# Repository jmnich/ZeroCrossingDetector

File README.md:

# Zero Crossing Detector (ZCD) 
*Designed for use with Fourier Transform Spectrometers.* 
This device converts symmetric sinusoidal signal from the reference beam detector into a TTL-compatible trigger for acquisition. 

Main features: 
- two TTL outputs 
- one intermediate monitor output
- one input 
- requires an external +-5 V symmetric supply
- accepts signals up to 20 V AC peak-peak +- 10 V DC
- input frequency up to 5 MHz
- hysteresis selectable with a rotary switch from about 20mV up to 2V

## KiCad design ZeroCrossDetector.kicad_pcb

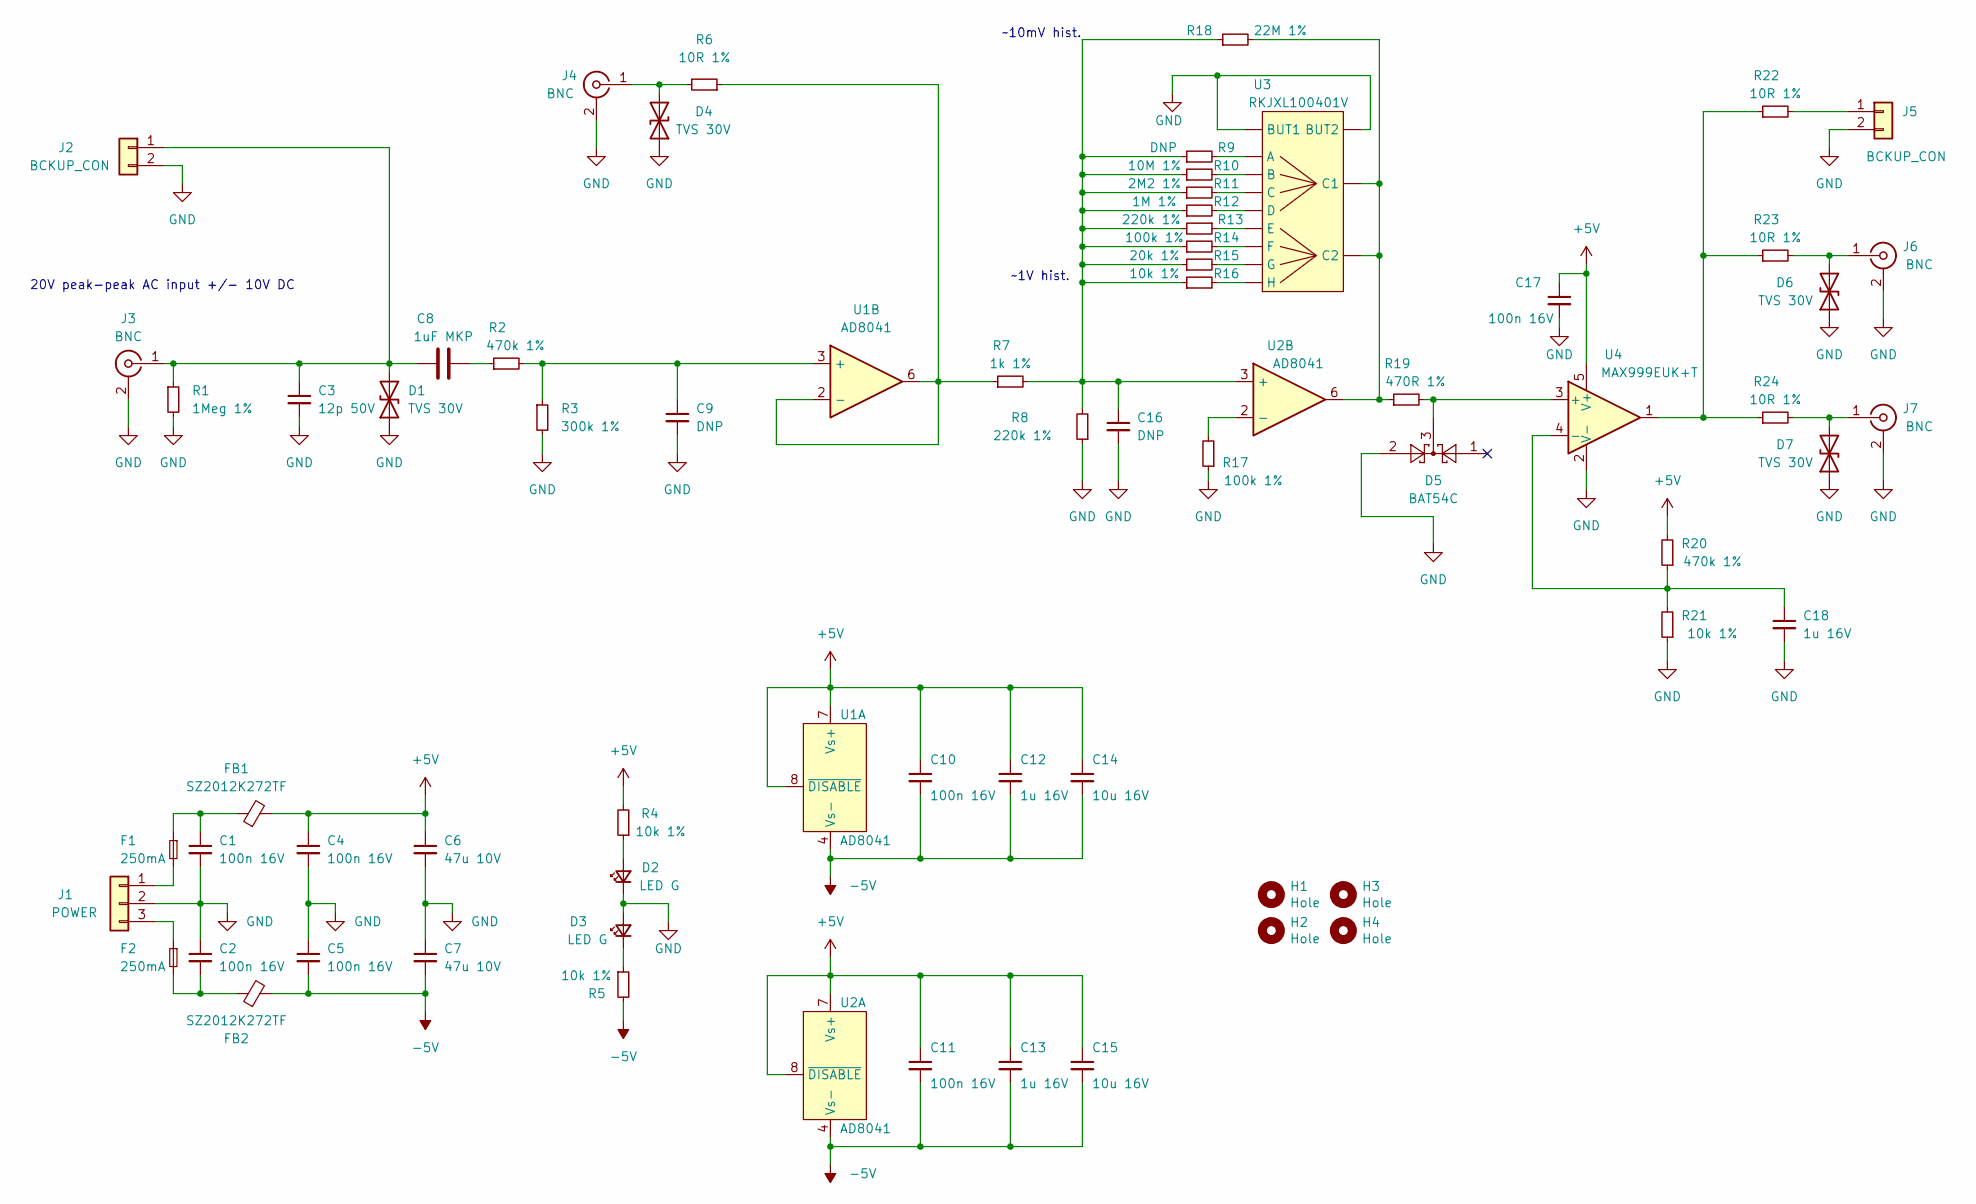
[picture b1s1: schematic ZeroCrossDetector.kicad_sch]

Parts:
C1, C2, C4, C5, C10, C11, C17: 100n 16V; C_0603_1608Metric; JLC C14663
C3: 12p 50V; C_0603_1608Metric; JLC C38523
C6, C7: 47u 10V; C_1206_3216Metric; JLC C96123
C8: 1uF MKP; C_Rect_L7.5mm_W6.5mm_P5.00mm; JLC C514201
C9, C16: DNP; C_0603_1608Metric
C12, C13, C18: 1u 16V; C_0603_1608Metric; JLC C15849
C14, C15: 10u 16V; C_0805_2012Metric; JLC C96446
D1, D4, D6, D7: TVS 30V; D_SMB; MPN SMBJ30CA/TR13; JLC C78418
D2, D3: LED G; LED_0603_1608Metric_Pad1.05x0.95mm_HandSolder; JLC C72043
D5: BAT54C; SOT-23; JLC C37704
F1, F2: 250mA; Fuse_0805_2012Metric_Pad1.15x1.40mm_HandSolder; JLC C269102
FB1, FB2: SZ2012K272TF; L_0805_2012Metric; MPN SZ2012K272TF; JLC C185876
H1, H2, H3, H4: Hole; MountingHole_3.2mm_M3_Pad_Via
J1: POWER; TerminalBlock_Phoenix_MKDS-1,5-3-5.08_1x03_P5.08mm_Horizont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; MPN DG500-5.08-03P-14-00A(H); JLC C581322
J2, J5: BCKUP_CON; PinHeader_1x02_P2.54mm_Vertical
J3, J4, J6, J7: BNC; BNC_Amphenol_B6252HB-NPP3G-50_Horizontal; JLC C2837587
R1: 1Meg 1%; R_0805_2012Metric_Pad1.20x1.40mm_HandSolder; JLC C17514
R2, R20: 470k 1%; R_0805_2012Metric_Pad1.20x1.40mm_HandSolder; JLC C17709
R3: 300k 1%; R_0805_2012Metric_Pad1.20x1.40mm_HandSolder; JLC C17616
R4, R5: 10k 1%; R_0603_1608Metric_Pad0.98x0.95mm_HandSolder; JLC C25804
R6, R22, R23, R24: 10R 1%; R_0805_2012Metric_Pad1.20x1.40mm_HandSolder; JLC C17415
R7: 1k 1%; R_0805_2012Metric_Pad1.20x1.40mm_HandSolder; JLC C17513
R8, R13: 220k 1%; R_0805_2012Metric_Pad1.20x1.40mm_HandSolder; JLC C17556
R9: DNP; R_0805_2012Metric_Pad1.20x1.40mm_HandSolder
R10: 10M 1%; R_0805_2012Metric_Pad1.20x1.40mm_HandSolder; JLC C26108
R11: 2M2 1%; R_0805_2012Metric_Pad1.20x1.40mm_HandSolder; JLC C26113
R12: 1M 1%; R_0805_2012Metric_Pad1.20x1.40mm_HandSolder; JLC C17514
R14, R17: 100k 1%; R_0805_2012Metric_Pad1.20x1.40mm_HandSolder; JLC C149504
R15: 20k 1%; R_0805_2012Metric_Pad1.20x1.40mm_HandSolder; JLC C4328
R16, R21: 10k 1%; R_0805_2012Metric_Pad1.20x1.40mm_HandSolder; JLC C17414
R18: 22M 1%; R_0805_2012Metric_Pad1.20x1.40mm_HandSolder; JLC C62398
R19: 470R 1%; R_0805_2012Metric_Pad1.20x1.40mm_HandSolder; JLC C17710
U1, U2: AD8041; SOIC-8_3.9x4.9mm_P1.27mm; MPN AD8041ARZ; JLC C90472
U3: RKJXL100401V; MPN RKJXL100401V; JLC C160838
U4: MAX999EUK+T; SOT-23-5; MPN MAX999EUK+T; JLC C124667

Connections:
+5V: C4.1, C6.1, C10.1, C11.1, C12.1, C13.1, C14.1, C15.1, C17.1, FB1.2, R4.2, R20.2, U1.7 (Vs+), U1.8 (~DISABLE), U2.7 (Vs+), U2.8 (~DISABLE), U4.5 (V+)
-5V: C5.2, C7.2, C10.2, C11.2, C12.2, C13.2, C14.2, C15.2, FB2.2, R5.2, U1.4 (Vs-), U2.4 (Vs-)
GND: C1.2, C2.1, C3.2, C4.2, C5.1, C6.2, C7.1, C9.2, C16.2, C17.2, C18.2, D1.1 (A1), D2.1 (K), D3.2 (A), D4.1 (A1), D5.2, D6.1 (A1), D7.1 (A1), J1.2, J2.2, J3.2 (Ext), J4.2 (Ext), J5.2, J6.2 (Ext), J7.2 (Ext), R1.2, R3.2, R8.1, R17.1, R21.1, U3.1 (BUT1), U3.2 (BUT2), U4.2 (V-)
unnamed: C1.1, F1.1, FB1.1
unnamed: C2.2, F2.2, FB2.1
unnamed: C3.1, C8.1, D1.2 (A2), J2.1, J3.1 (In), R1.1
unnamed: C8.2, R2.1
unnamed: C9.1, R2.2, R3.1, U1.3 (+)
unnamed: C16.1, R7.2, R8.2, R9.1, R10.1, R11.1, R12.1, R13.2, R14.1, R15.1, R16.1, R18.1, U2.3 (+)
unnamed: C18.1, R20.1, R21.2, U4.4 (-)
unnamed: D2.2 (A), R4.1
unnamed: D3.1 (K), R5.1
unnamed: D4.2 (A2), J4.1 (In), R6.2
unnamed: D5.3, R19.2, U4.3 (+)
unnamed: D6.2 (A2), J6.1 (In), R23.2
unnamed: D7.2 (A2), J7.1 (In), R24.2
unnamed: F1.2, J1.1
unnamed: F2.1, J1.3
unnamed: J5.1, R22.2
unnamed: R6.1, R7.1, U1.2 (-), U1.6
unnamed: R9.2, U3.A
unnamed: R17.2, U2.2 (-)
unnamed: R18.2, R19.1, U2.6, U3.C1, U3.C2
unnamed: R22.1, R23.1, R24.1, U4.1
unnamed: R10.2, U3.B
unnamed: R11.2, U3.C
unnamed: R12.2, U3.D
unnamed: R13.1, U3.E
unnamed: R14.2, U3.F
unnamed: R15.2, U3.G
unnamed: R16.2, U3.H

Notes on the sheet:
~1V hist.
20V peak-peak AC input +/- 10V DC
~10mV hist.

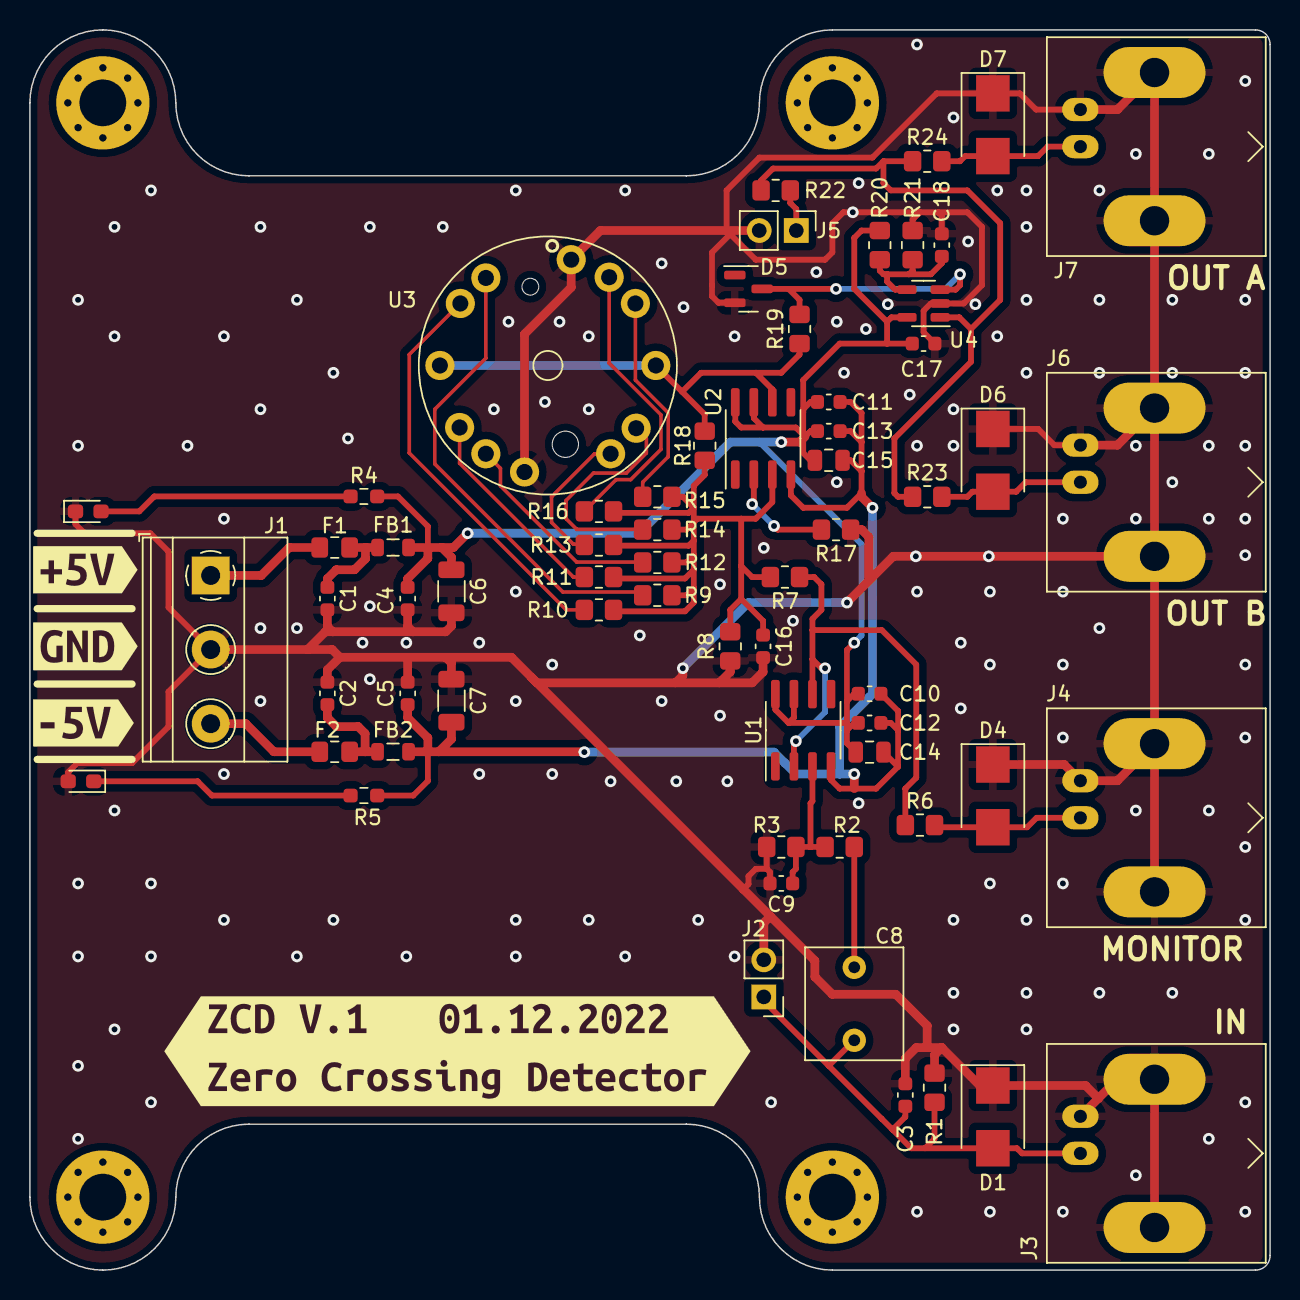
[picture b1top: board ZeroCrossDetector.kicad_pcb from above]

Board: 2 copper layers, 85.0 x 85.0 mm, 72 parts (0 on the bottom side), 31 nets.

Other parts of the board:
kibuzzard-63889D11: G***; kibuzzard-63889D11
kibuzzard-63889DAC: G***; kibuzzard-63889DAC
kibuzzard-63889DB6: G***; kibuzzard-63889DB6
kibuzzard-63889DBE: G***; kibuzzard-63889DBE

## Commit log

2022-12-01 readme
2022-12-02 resistor values decreased
